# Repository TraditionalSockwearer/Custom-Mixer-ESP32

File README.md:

# Custom Mixer ESP32 (v2.0)

This project uses an ESP32 to read 5 linear faders, 2 rotary encoders, and 18 switches, with programmable buttons acting like MIDI and everything that happens, as a change in volume will show on the 2.2-inch screen.

This project's purpose is to act as a mixer and control the volume of an app when it sounds too loud or too quiet.

The Rotary Encoders will be used as a selector to scroll through active apps and the slider they should be on, or potentially as a master volume control.

## Schematic

## PCB

## CAD

## Quick Start

### 1. Flash the ESP32-S3 Firmware

1. Install [CircuitPython 9.x](https://circuitpython.org/board/espressif_esp32s3_devkitc_1_n8r8/) on your ESP32-S3
2. Copy `Firmware/esp32/main.py` and `Firmware/esp32/boot.py` to the **CIRCUITPY** drive
3. Copy these libraries to the `/lib` folder on the drive (from the [CircuitPython Bundle](https://circuitpython.org/libraries)):
   - `adafruit_ili9341.mpy`
   - `adafruit_display_text/`
   - `adafruit_bus_device/`

### 2. Run the PC Software

```bash
pip install pycaw pyserial pystray psutil Pillow pywin32 obs-websocket-py
python Firmware/mixer.py --console
```

Run `python Firmware/mixer.py --help` for all options (COM port override, test mode, etc.).

> Requires **Windows 10/11**, **Python 3.10+**, and optionally **EqualizerAPO** (for EQ mode) and **OBS with WebSocket** (for OBS channel).

## Firmware

[View detailed firmware documentation](Firmware/README.md)

## BOM

The complete list of hardware required to build this project.

### Digikey

| Part | Description | Qty | Price |
| :--- | :--- | :--- | :--- |
| **[PTA6043-2015CPB103](https://www.digikey.co.uk/en/products/detail/bourns-inc/PTA6043-2015CPB103/3781230)** | Bourns — Slide Pot 10K, 60mm | 5 | £7.10 |
| **[K104K10X7RF5UH5](https://www.digikey.co.uk/en/products/detail/vishay-beyschlag-draloric-bc-components/K104K10X7RF5UH5/2356754)** | Vishay — Ceramic Cap 0.1µF 50V | 10 | £1.13 |
| **[ECA-1EM101B](https://www.digikey.co.uk/en/products/detail/panasonic-electronic-components/ECA-1EM101B/268461)** | Panasonic — Electrolytic Cap 100µF 25V | 2 | £0.46 |
| **[PEC11R-4215F-S0024](https://www.digikey.co.uk/en/products/detail/bourns-inc/PEC11R-4215F-S0024/4499665)** | Bourns — Rotary Encoder | 2 | £3.30 |
| **[PRPC040SAAN-RC](https://www.digikey.co.uk/en/products/detail/sullins-connector-solutions/PRPC040SAAN-RC/2775214)** | Sullins — 40-Pin Header | 3 | £1.23 |
| **[RNF14FTD10K0](https://www.digikey.co.uk/en/products/detail/stackpole-electronics-inc/RNF14FTD10K0/1706596)** | Stackpole — 10K Resistor 1/4W | 10 | £0.30 |
| **[CFR-50JT-52-4K7](https://www.digikey.co.uk/en/products/detail/yageo/CFR-50JT-52-4K7/9099664)** | YAGEO — 4.7K Resistor 1/2W | 10 | £0.34 |
| **[OEJL-90-4-5](https://www.digikey.co.uk/en/products/detail/kilo-international/OEJL-90-4-5/710678)** | Kilo International — Solid Aluminium Knob | 2 | £18.68 |
| **[1300-B](https://www.digikey.co.uk/en/products/detail/davies-molding-llc/1300-B/7908413)** | Davies Molding — Nylon Knob | 5 | £3.86 |
| **[MCP23017-E/SP](https://www.digikey.co.uk/en/products/detail/microchip-technology/MCP23017-E-SP/894272)** | Microchip — I²C I/O Expander 28-SDIP | 2 | £2.54 |

Digikey Total: £45.37

### AliExpress

| Part | Description | Qty | Price |
| :--- | :--- | :--- | :--- |
| **[2.2" TFT LCD](https://www.aliexpress.com/item/1005008143782445.html)** | 2.2" ILI9341 Full Color TFT (includes shipping) | 1 | £5.22 + £3.32 shipping |
| **[ESP32-S3-WROOM-1 N16R8](https://www.aliexpress.com/item/1005008796158734.html)** | ESP32-S3 Dev Board, 44-Pin, 8M PSRAM | 1 | £5.28 |
| **Cherry MX Switches** | Pre-owned mechanical switches | 18 | £0.00 |

Estimated AliExpress Total: £13.82 without discount

### Manufacturing

| Part | Description | Qty | Price |
| :--- | :--- | :--- | :--- |
| **[JLCPCB PCB](https://jlcpcb.com/)** | PCB prototype (black, 1.6mm, HASL with lead) | 5 | $13.10 |

JLCPCB Total: $21.08 or £15.80

For 3D printing, filament is about £10.25 from Bambu Labs.

**Grand Total: £85.24**

## KiCad Libraries

- [SSD1306 OLED Footprint](https://github.com/gorbachev/KiCad-SSD1306-0.91-OLED-4pin-128x32.pretty/tree/master)
- [ESP32-DEVKITC-32E](https://www.snapeda.com/parts/ESP32-DEVKITC-32E/Espressif%20Systems/view-part/?ref=search&t=esp32&ab_test_case=b)
- [PEC12R Rotary Encoder](https://www.snapeda.com/parts/PEC12R-4217F-S0024/Bourns/view-part/?ref=search&t=rotary%20encoder)
- [Adafruit 2717](https://www.snapeda.com/parts/2717/Adafruit%20Industries/view-part/)
- [PTA4543 Slide Pot](https://www.snapeda.com/parts/PTA4543-2015DPA103/Bourns/view-part/?ref=search&t=PTA4543-2015DPA103&ab_test_case=b)
- [0.91" OLED 3D Model](https://grabcad.com/library/0-91-oled-display-module-1/files?folder_id=13981557)

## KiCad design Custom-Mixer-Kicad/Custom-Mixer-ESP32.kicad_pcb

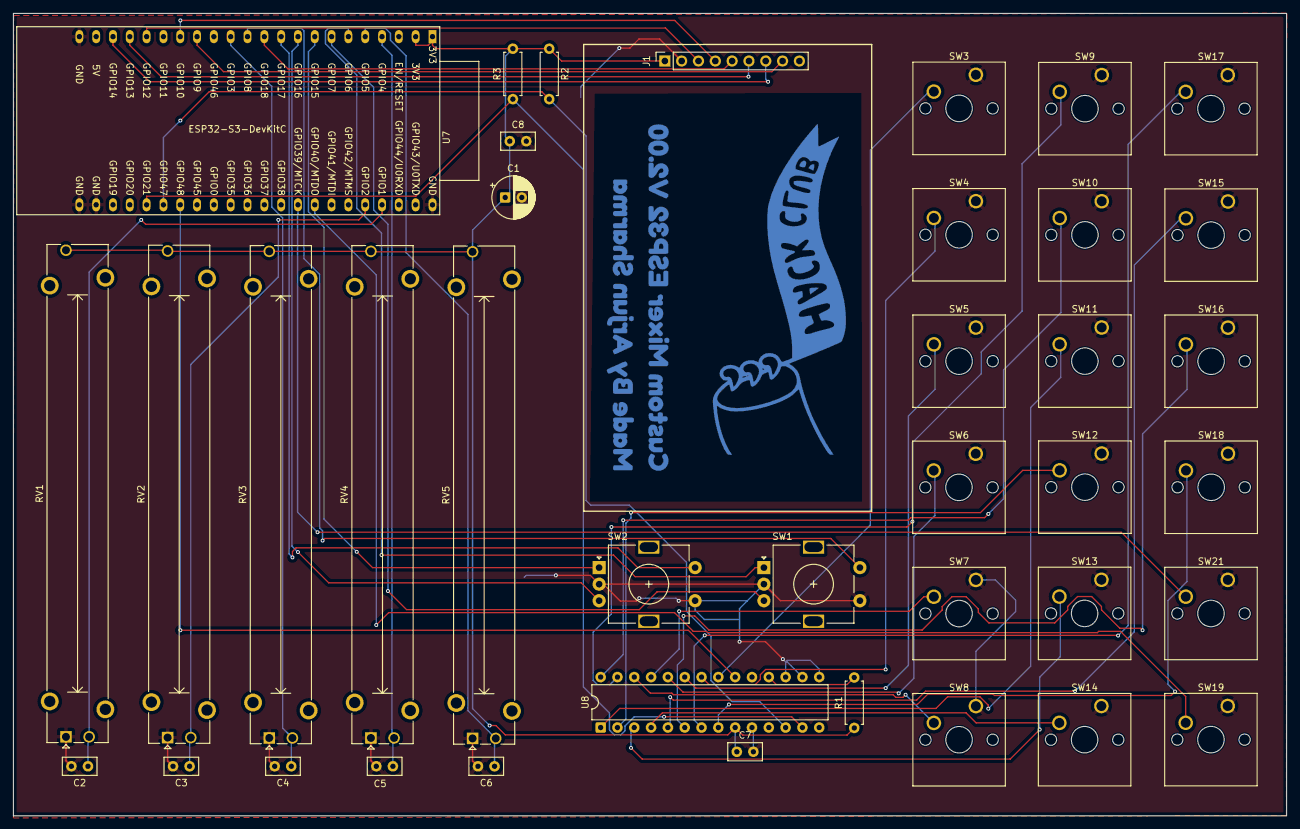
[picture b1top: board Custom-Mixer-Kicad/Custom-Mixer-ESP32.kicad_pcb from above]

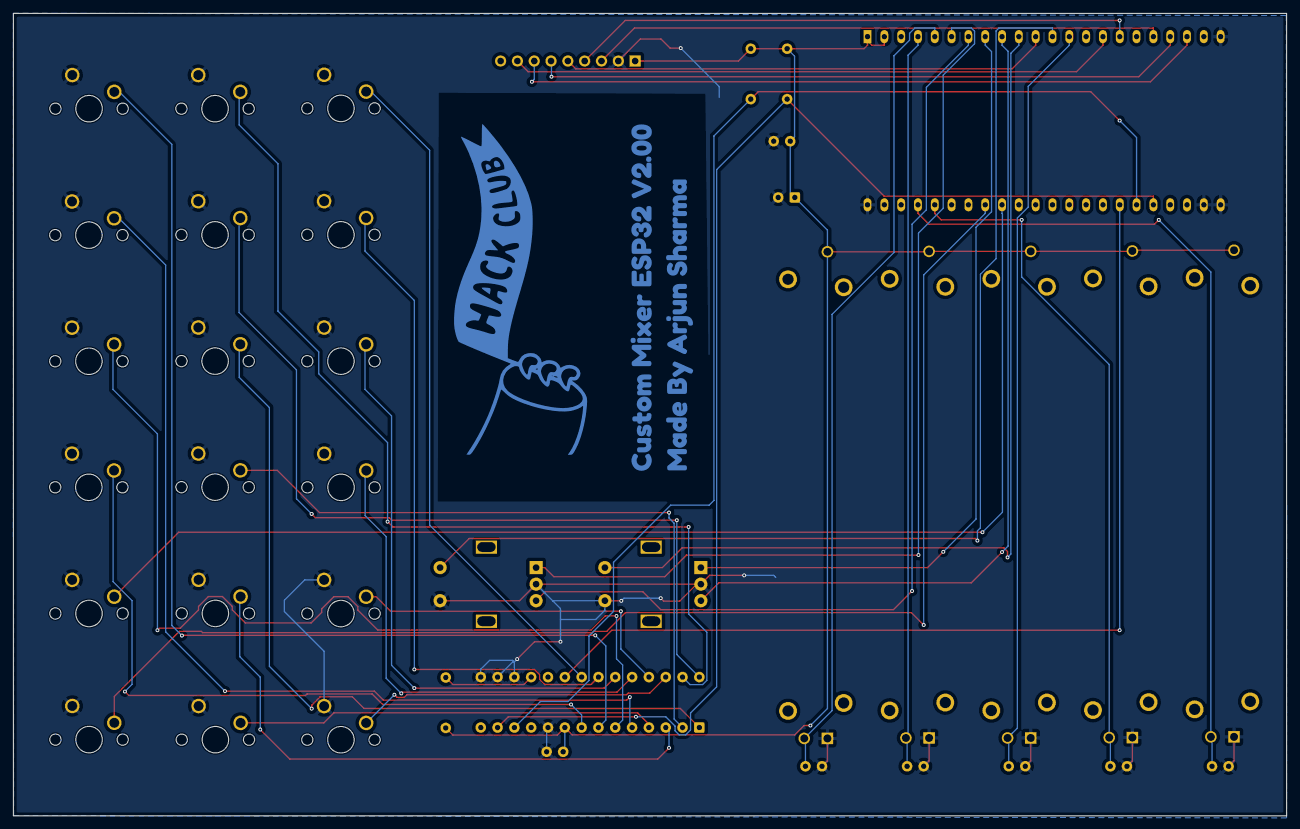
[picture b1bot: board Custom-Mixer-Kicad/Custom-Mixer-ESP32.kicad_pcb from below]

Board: 2 copper layers, 192.3 x 121.2 mm, 41 parts (2 on the bottom side), 41 nets.

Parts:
C1: 100µF; CP_Radial_D6.3mm_P2.50mm
C2, C3, C4, C5, C6, C7, C8: 0.1µF; C_Disc_D5.0mm_W2.5mm_P2.50mm
Goo: LOGO; Hackclublogo(fmask)
J1: Conn_01x08; PinSocket_1x09_P2.54mm_Vertical
R1: 10K; R_Axial_DIN0207_L6.3mm_D2.5mm_P7.62mm_Horizontal
R2, R3: 4.7K; R_Axial_DIN0207_L6.3mm_D2.5mm_P7.62mm_Horizontal
RV1, RV2, RV3, RV4, RV5: R_Potentiometer_Dual; Potentiometer_Bourns_PTA6043_Single_Slide
SW1, SW2: RotaryEncoder_Switch; RotaryEncoder_Alps_EC11E-Switch_Vertical_H20mm
SW3, SW4, SW5, SW6, SW7, SW8, SW9, SW10, SW11, SW12, SW13, SW14, SW15, SW16, SW17, SW18, SW19, SW21: SW_Push; SW_Cherry_MX_1.00u_PCB
U7: ESP32-S3-DevKitC
U8: MCP23017_SP; DIP-28_W7.62mm
kibuzzard-698F8E64: G***; kibuzzard-698F8E64

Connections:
+3V3: C1.1, C7.1, C8.1, J1.1, R1.1, R2.1, R3.2, RV1.3, RV2.3, RV3.3, RV4.3, RV5.3, U7.1 (3V3), U7.2 (3V3), U8.9 (VDD)
BL: J1.8, U7.15 (GPIO9/ADC1_CH8)
CLK: J1.7, U7.20 (GPIO14/ADC2_CH3)
CS: J1.3, U7.18 (GPIO12/ADC2_CH1)
DC: J1.5, U7.11 (GPIO18/ADC2_CH7)
GND: C1.2, C2.2, C3.2, C4.2, C5.2, C6.2, C7.2, C8.2, J1.2, RV1.1, RV2.1, RV3.1, RV4.1, RV5.1, SW1.C, SW1.S1, SW2.C, SW2.S1, SW3.1, SW4.1, SW5.1, SW6.1, SW7.1, SW8.1, SW9.1, SW10.1, SW11.1, SW12.1, SW13.1, SW14.1, SW15.1, SW16.1, SW17.1, SW18.1, SW19.1, SW21.1, U7.22 (GND), U7.23 (GND), U7.24 (GND), U7.44 (GND), U8.10 (VSS), U8.15 (A0), U8.16 (A1), U8.17 (A2)
GPIO 1: C2.1, RV1.2, U7.41 (GPIO1/ADC1_CH0)
GPIO 2: C3.1, RV2.2, U7.40 (GPIO2/ADC1_CH1)
GPIO 3: C4.1, RV3.2, U7.13 (GPIO3/ADC1_CH2)
GPIO 4: C5.1, RV4.2, U7.4 (GPIO4/ADC1_CH3)
GPIO 5: C6.1, RV5.2, U7.5 (GPIO5/ADC1_CH4)
GPIO 6: SW1.A, U7.6 (GPIO6/ADC1_CH5)
GPIO 7: SW1.B, U7.7 (GPIO7/ADC1_CH6)
GPIO 8: SW1.S2, U7.12 (GPIO8/ADC1_CH7)
GPIO 15: SW2.A, U7.8 (GPIO15/ADC2_CH4/32K_P)
GPIO 16: SW2.B, U7.9 (GPIO16/ADC2_CH5/32K_N)
GPIO 17: SW2.S2, U7.10 (GPIO17/ADC2_CH6)
GPIO 39: SW21.2, U7.36 (GPIO39/MTCK)
GPIO 40: SW19.2, U7.37 (GPIO40/MTDO)
MOSI: J1.6, U7.19 (GPIO13/ADC2_CH2)
unnamed: U7.29 (GPIO48), U8.20 (INTA)
unnamed: R1.2, U8.18 (~RESET)
RST: J1.4, U7.16 (GPIO10/ADC1_CH9)
SCL: R2.2, U7.28 (GPIO47), U8.12 (SCK)
SDA: R3.1, U7.27 (GPIO21), U8.13 (SDA)
a0: SW3.2, U8.21 (GPA0)
a1: SW4.2, U8.22 (GPA1)
a2: SW5.2, U8.23 (GPA2)
a3: SW6.2, U8.24 (GPA3)
a4: SW7.2, U8.25 (GPA4)
a5: SW8.2, U8.26 (GPA5)
a6: SW9.2, U8.27 (GPA6)
a7: SW10.2, U8.28 (GPA7)
b0: SW11.2, U8.1 (GPB0)
b1: SW12.2, U8.2 (GPB1)
b2: SW13.2, U8.3 (GPB2)
b3: SW14.2, U8.4 (GPB3)
b4: SW15.2, U8.5 (GPB4)
b5: SW16.2, U8.6 (GPB5)
b6: SW17.2, U8.7 (GPB6)
b7: SW18.2, U8.8 (GPB7)

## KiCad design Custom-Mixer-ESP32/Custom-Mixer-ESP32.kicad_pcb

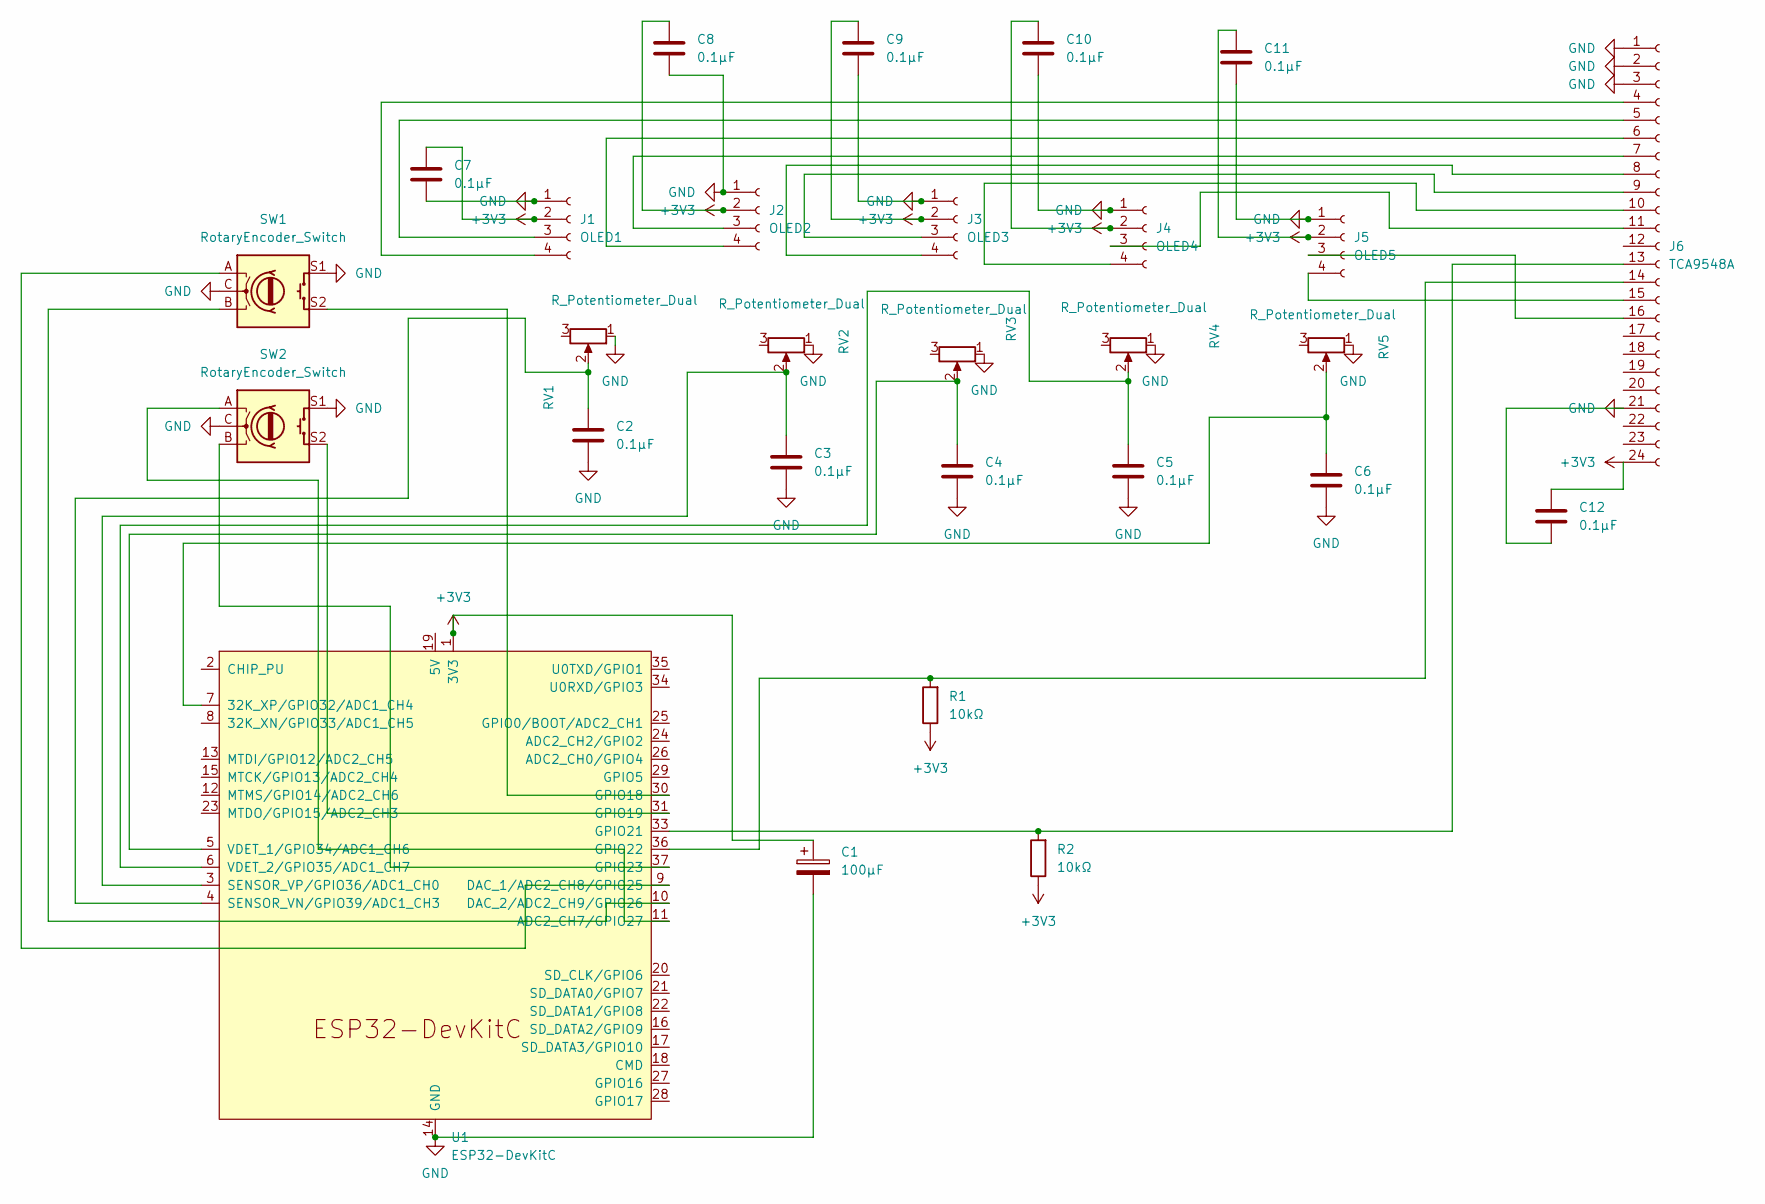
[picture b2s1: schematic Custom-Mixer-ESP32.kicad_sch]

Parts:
C1: 100µF; CP_Radial_D6.3mm_P2.50mm
C2, C3, C4, C5, C6, C7, C8, C9, C10, C11, C12: 0.1µF; C_Disc_D5.0mm_W2.5mm_P2.50mm
J1: OLED1; SSD1306-0.91-OLED-4pin-128x32
J2: OLED2; SSD1306-0.91-OLED-4pin-128x32
J3: OLED3; SSD1306-0.91-OLED-4pin-128x32
J4: OLED4; SSD1306-0.91-OLED-4pin-128x32
J5: OLED5; SSD1306-0.91-OLED-4pin-128x32
J6: TCA9548A; MODULE_2717
R1, R2: 10kΩ; R_Axial_DIN0207_L6.3mm_D2.5mm_P10.16mm_Horizontal
RV1, RV2, RV3, RV4, RV5: R_Potentiometer_Dual; Potentiometer_Bourns_PTA6043_Single_Slide
SW1, SW2: RotaryEncoder_Switch; RotaryEncoder_Alps_EC11E-Switch_Vertical_H20mm
U1: ESP32-DevKitC

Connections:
+3V3: C1.1, C7.1, C8.1, C9.1, C10.1, C11.1, C12.1, J1.2, J2.2, J3.2, J4.2, J5.2, J6.24, R1.1, R2.1, U1.1 (3V3)
GND: C1.2, C2.2, C3.2, C4.2, C5.2, C6.2, C7.2, C8.2, C9.2, C10.2, C11.2, C12.2, J1.1, J2.1, J3.1, J4.1, J5.1, J6.1, J6.2, J6.3, J6.21, RV1.1, RV2.1, RV3.1, RV4.1, RV5.1, SW1.C, SW1.S1, SW2.C, SW2.S1, U1.14 (GND), U1.32 (GND), U1.38 (GND)
unnamed: J1.3, J6.5
unnamed: J1.4, J6.4
unnamed: J2.3, J6.7
unnamed: J2.4, J6.6
unnamed: J3.3, J6.9
unnamed: J3.4, J6.8
unnamed: J4.3, J6.11
unnamed: J4.4, J6.10
unnamed: J5.3, J6.16
unnamed: J5.4, J6.15
unnamed: J6.13, R2.2, U1.33 (GPIO21)
unnamed: J6.14, R1.2, U1.36 (GPIO22)
unnamed: C6.1, RV5.2, U1.7 (32K_XP/GPIO32/ADC1_CH4)
unnamed: SW2.A, U1.11 (ADC2_CH7/GPIO27)
unnamed: SW1.A, U1.9 (DAC_1/ADC2_CH8/GPIO25)
unnamed: SW1.B, U1.10 (DAC_2/ADC2_CH9/GPIO26)
unnamed: SW1.S2, U1.30 (GPIO18)
unnamed: SW2.S2, U1.31 (GPIO19)
unnamed: SW2.B, U1.37 (GPIO23)
unnamed: C2.1, RV1.2, U1.4 (SENSOR_VN/GPIO39/ADC1_CH3)
unnamed: C3.1, RV2.2, U1.3 (SENSOR_VP/GPIO36/ADC1_CH0)
unnamed: C4.1, RV3.2, U1.5 (VDET_1/GPIO34/ADC1_CH6)
unnamed: C5.1, RV4.2, U1.6 (VDET_2/GPIO35/ADC1_CH7)

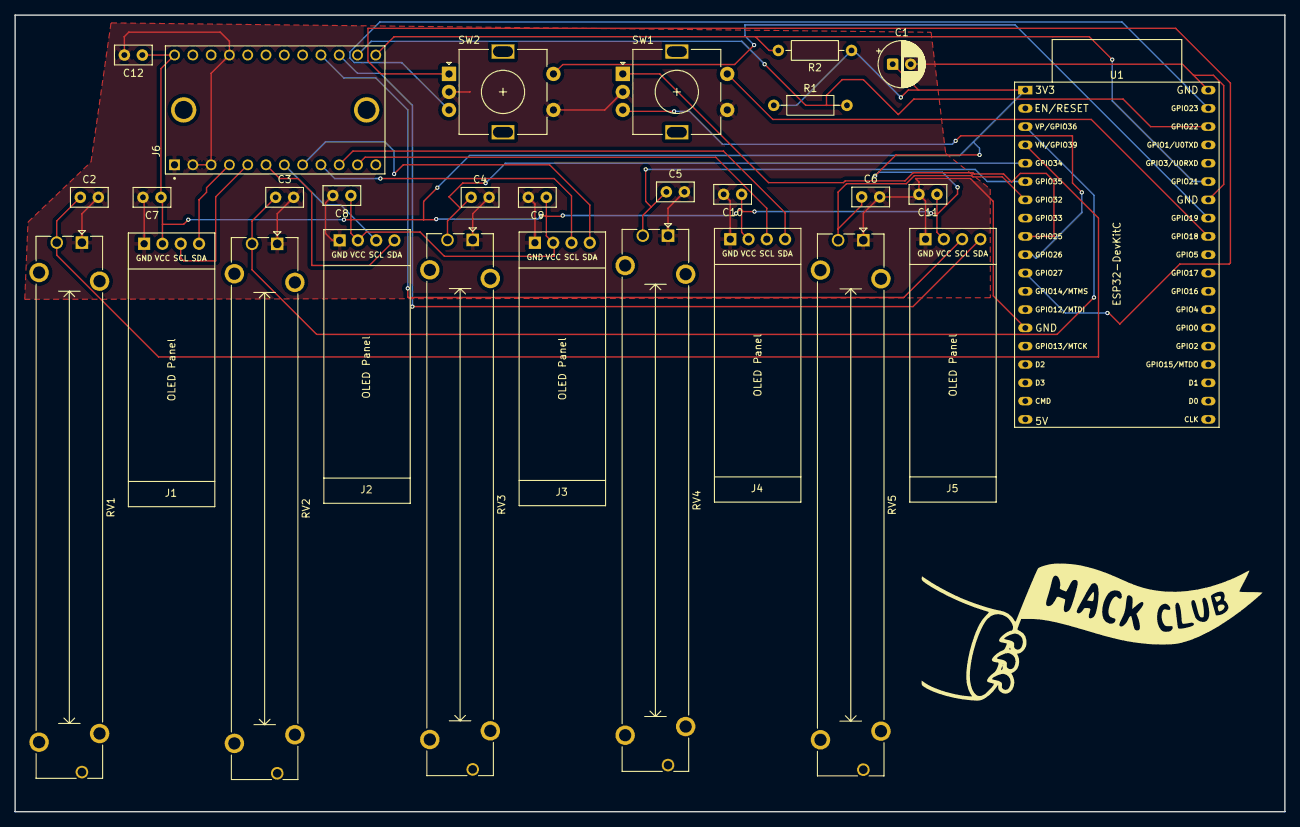
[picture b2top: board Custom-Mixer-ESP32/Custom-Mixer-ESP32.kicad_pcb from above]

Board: 2 copper layers, 176.3 x 110.6 mm, 28 parts (0 on the bottom side), 25 nets.

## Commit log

2026-01-24 First Revision
2026-01-25 Add Gerber and drill files for Custom-Mixer-ESP32 PCB
    Initial commit of all generated Gerber, drill, and job files for the Custom-Mixer-ESP32 PCB design. These files are required for PCB fabrication and assembly.
2026-01-25 Initialize README with project details and BOM
    Added project description, bill of materials, and hardware details.
2026-01-25 Update README with schematic and PCB images
    Added schematic and PCB images to the README.
2026-01-25 Add assembly PDF and board2pdf config for ESP32 PCB
    Added Custom-Mixer-ESP32__Assembly.pdf and board2pdf.config.ini for generating assembly documentation. Updated the PCB file to change drill shape output settings. Assembly PDF is also included in the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
2026-01-25 Add BOM and project CSV files, update .gitignore
    Added BOM.csv and Custom-Mixer-ESP32.csv to track bill of materials and project components. Updated .gitignore to allow CSV and XML files to be committed, enabling version control of exported BOMs.
2026-01-25 Revise README for Custom Mixer ESP32 project
    Updated project name and clarified functionality. Added links for components and reorganized sections for better clarity.
2026-01-25 Redo File directory and 2nd revision of PCB and schematic
2026-01-25 Convert hardware links to markdown format
    Updated links in the hardware requirements section to use markdown format.
2026-01-25 Add Adafruit CircuitPython libraries to firmware
    Added a large set of Adafruit CircuitPython .mpy and __init__.py libraries to the Firmware/lib directory. This update integrates support for a wide range of sensors, displays, communication modules, 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
2026-01-25 Update BOM: adjust quantities and add multiplexer
    Reduced ceramic capacitor quantity from 15 to 10, removed resistor line, added TCA9548A I2C multiplexer, and updated total cost in the BOM.csv file.
2026-01-25 Remove unused wires from schematic
    Deleted several unused wire
2026-01-27 Update README with new images and BOM entry
    Added additional images for PCB and CAD sections, and included a new component in the BOM.
2026-01-29 Cad Revision
2026-01-29 Connect potentiometer pads to +3V3 and clean up nets
    Updated RV2, RV3, and RV4 potentiometer pad 3 connections from unconnected nets to +3V3. Cleaned up and renumbered net assignments throughout the schematic, removed unused/unconnected net definitions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
2026-01-29 Add +3V3 power symbols and update PCB routing
    Added multiple +3V3 power symbols to the schematic for improved clarity and power distribution. Updated PCB routing for nets 1 and 7, including new segments, vias, and changes to net connections for 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
2026-02-02 Add MCP23017 PCB project & update KiCad libs
    Add Adafruit MCP23017 GPIO Expander KiCad project (board, schematic, MCP23017 symbol/footprint, README, license, assets and pretty library parts). Add OLED 128x64 symbol/module files. Modify Custom-M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
2026-02-06 Rewire and create custom footprint
2026-02-13 Complete Wire Revamp
2026-02-13 PCB rework completed
2026-02-14 Revise README for Custom Mixer ESP32 to v2.0
    Updated project details to reflect new features and components in version 2.0, including additional switches and improved functionality.
2026-02-14 PCB Completion and GerberFiles Created
2026-02-15 Update BOM: parts, quantities, prices, and total
    Adjust BOM entries and pricing: lower ceramic capacitor unit price; replace ESP32-DEVKITC with ESP32-S3-WROOM-1; add resistor packs, premium and standard knobs, MCP23017 I2C expander, a 2.2" TFT scre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
2026-03-21 Restructure and add firmware
2026-03-21 Update BOM and some parts of readme
